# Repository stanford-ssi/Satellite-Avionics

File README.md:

# Satellite-Avionics

Welcome to SSI **Satellite Avionics**! Here, you can find everything you need to navigate our team! This repository covers weekly meeting times, technical trainings, team design documentation, assembly processes, testing procedures, and so much more!

**If you're new to Satellite Avionics, (and of course, are a stanford student), you should look through the [Satellite Avionics Onboarding Document](https://docs.google.com/document/d/1Evk9vAAE3cXXHKh05v-SdmLuFbIsvqwTA4ssfbo16VE/edit?tab=t.0) to get started on our team!**

If you have any questions, feel free to contact any AV Co-lead on Slack! Or feel free to email Kale, the current AV co-lead repo manager at **kalesrz@stanford.edu**.

# Current Leadership (Spring 2026 - Winter 2027)
Satellite Avionics Co-Leads: 
 * Clara Zhen (czhen@stanford.edu)
 * Nimalan Anbhuarasan (nimalan@stanford.edu)
 * Kale Suarez (kalesrz@stanford.edu)

Satellite Co-Leads: 
 * Amy Zheng (amyzheng@stanford.edu)
 * River Dowdy (rivdowdy@stanford.edu)
 * Carson Lauer (clauer@stanford.edu)

Workspace Manager: Clara Zhen
 - Contact For Questions Regarding ES3 and Durand Access

## Getting On Slack!
In order to join our weekly meetings, you'll need to join our slack to figure out where were meeting! You can join our slack by clicking [here](https://ssi-teams.slack.com/signup). Once you're on the slack, go ahead and add the [#satellite-avionics](https://ssi-teams.slack.com/archives/C2L29KW8J) channel. You should also make sure to join all of these important channels!
* [#satellite-avionics](https://ssi-teams.slack.com/archives/C2L29KW8J)
    - All AV communication and announcements happen here! You need to be in this channel to know
      where were meeting for the week.
* [#satellites](https://ssi-teams.slack.com/archives/C04JL94F9)
    - General Satellites team communications and announcements happen here!
* [#satellite-systems](https://ssi-teams.slack.com/archives/C4UL92684)
    - System-wide meeting plans and discussions with other subteams on Satellites happen here!
* [#esiii](https://ssi-teams.slack.com/archives/C3YLQTN87)
    - Our Lab Space!!!
* [#doorbell](https://ssi-teams.slack.com/archives/CE360LHD0)
    - If you don't have keycard access to End Station III (ES3), run the `\doorbell` command to get someone to come open the door if anyones in ES3.

## Weekly Meeting Times
Satellite Avionics has two official meetings each week:
**Weekly Avionics Meeting**
 * **Time:** Wednesday, 7:00 PM - 9:00 PM PST
 * **Location:** Check The [#Satellite-Avionics](https://ssi-teams.slack.com/archives/C2L29KW8J) channel in the slack for weekly meeting locations!
 * **Purpose:** Avionics meetings are specifically for AV-specific work, training, and discussions. AV member attendance is expected outside of conflicting Midterms or Finals. Fall quarter attendance is **mandatory** outside of class conflicts or personal health reasons.

**Satsurday Meetings**
 * **Time:** Saturday, 12:00 PM - 2:00 PM PST
 * **Location:** Check The [#Satellite-Avionics](https://ssi-teams.slack.com/archives/C2L29KW8J) channel in the slack for weekly meeting locations!
 * **Purpose**: Satsurday meetings are Satellite Avionics Full-Team work days! Every subteam will be meeting at this time. This can sometimes happen collectively and sometimes separately. Fall quarter will mostly be dedicated to AV specific onboarding training and early satellite development. Fall quarter attendance is **mandatory** outside of class conflicts or personal health reasons.

**Systems Meeting**
 * **Time:** Wednesday, 7:00 PM - 9:00 PM PST
 * **Location:** Check The [#Satellite-Systems](https://ssi-teams.slack.com/archives/C4UL92684) channel in the slack for weekly meeting locations!
 * **Purpose:** Systems meetings are where all major decisions about our satellite design occur and system-level planning and cross-team collaboration is planned. You are not obligated to come to these meetings if you are unable to, however, you should come to these meetings if you are available.

## Accessing Our Workspaces!
We primarily operate out of two buildings, End Station III (Deep Lab / Hepl South), and the Durand Aeronautics & Astronautics building. End Station III is a little difficult to find the first time, so please ask leads in the slack if you get lost!

### End Station III (Deep Lab / Hepl South)
**Address:** 491 S Service Rd, Stanford, CA 94305\
**Google Maps Link:** [Stanford Student Space Initiative](https://maps.app.goo.gl/ZUDnvgVmYYjSPFpS8)\
**Access Entrance:** Please enter through the **North Entrance** on Service Road (As Seen Below). After-Hours/Weekend Access requires that you obtain keycard access.

### Stanford University Aeronautics & Astronautics (Durand)
**Address:** 496 Lomita Mall, Stanford, CA 94305\
**Google Maps Link:** [Stanford University Aeronautics & Astronautics (Durand)](https://maps.app.goo.gl/TxbG7z5m1ypoC3tW7)\
**Access Entrance:** Any entrance can be used given you have obtained Durand keycard access. Otherwise, feel free to message a lead in the [#satellite-avionics](https://ssi-teams.slack.com/archives/C2L29KW8J) slack channel if you need help getting in!

### Gaining Access
To be able to gain keycard access to these workspaces and to be able to enter without another member to scan you in, you must complete the ES3 Lab safety trainings and complete all the steps listed on the [ES3 Access Guide](https://sites.google.com/stanford.edu/ssi/end-station-iii/keycard-access-for-es3). You will need to use your Stanford Email in order to view the guide.

## Additional Helpful Links / Quick Access
* [Stanford SSI Wiki: Satellites](https://ssi-wiki.stanford.edu/Category:Satellites)
    * SSI's official wiki page (notice: sometimes outdated, but there is some pretty useful information about the team and important definitions if you'd like to check it out.)\
* [SSI Slack Signup](https://ssi-teams.slack.com/signup)
* [ES3 Access Guide](https://sites.google.com/stanford.edu/ssi/end-station-iii/keycard-access-for-es3)

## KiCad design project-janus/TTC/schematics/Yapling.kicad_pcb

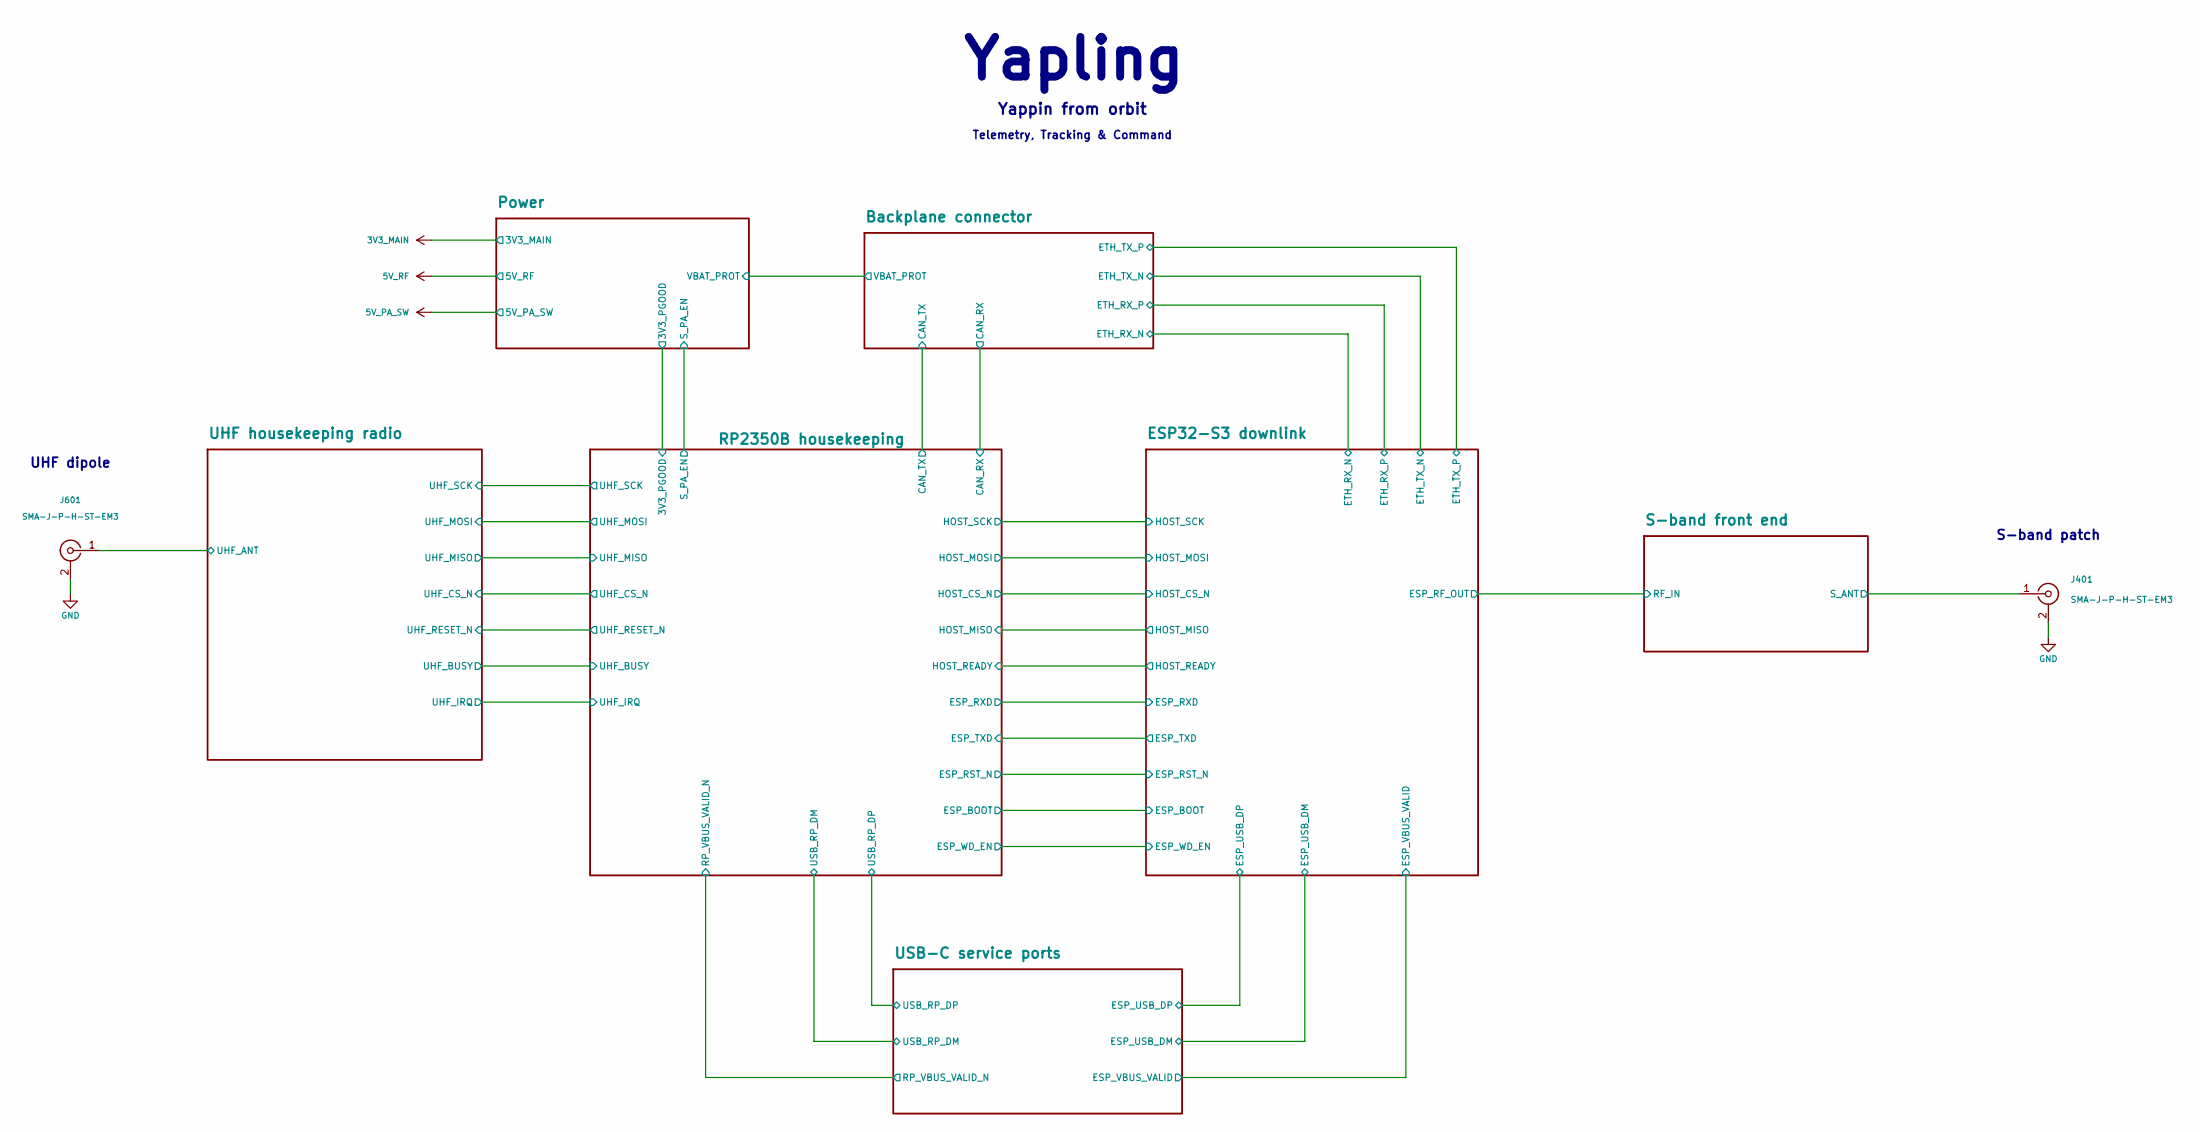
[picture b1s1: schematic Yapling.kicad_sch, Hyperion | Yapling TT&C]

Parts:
J401, J601: SMA-J-P-H-ST-EM3; Samtec_SMA_J_P_H_ST_EM3_DropInEdge; Rating 50 Ω, 335 V; MPN SMA-J-P-H-ST-EM3

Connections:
/S-band front end/S_ANT: J401.1 (In); also elsewhere on the board
/UHF housekeeping radio/UHF_ANT: J601.1 (In); also elsewhere on the board
GND: J401.2 (Ext), J601.2 (Ext); also elsewhere on the board

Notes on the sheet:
Yappin from orbit
Telemetry, Tracking & Command
UHF dipole
S-band patch
Yapling

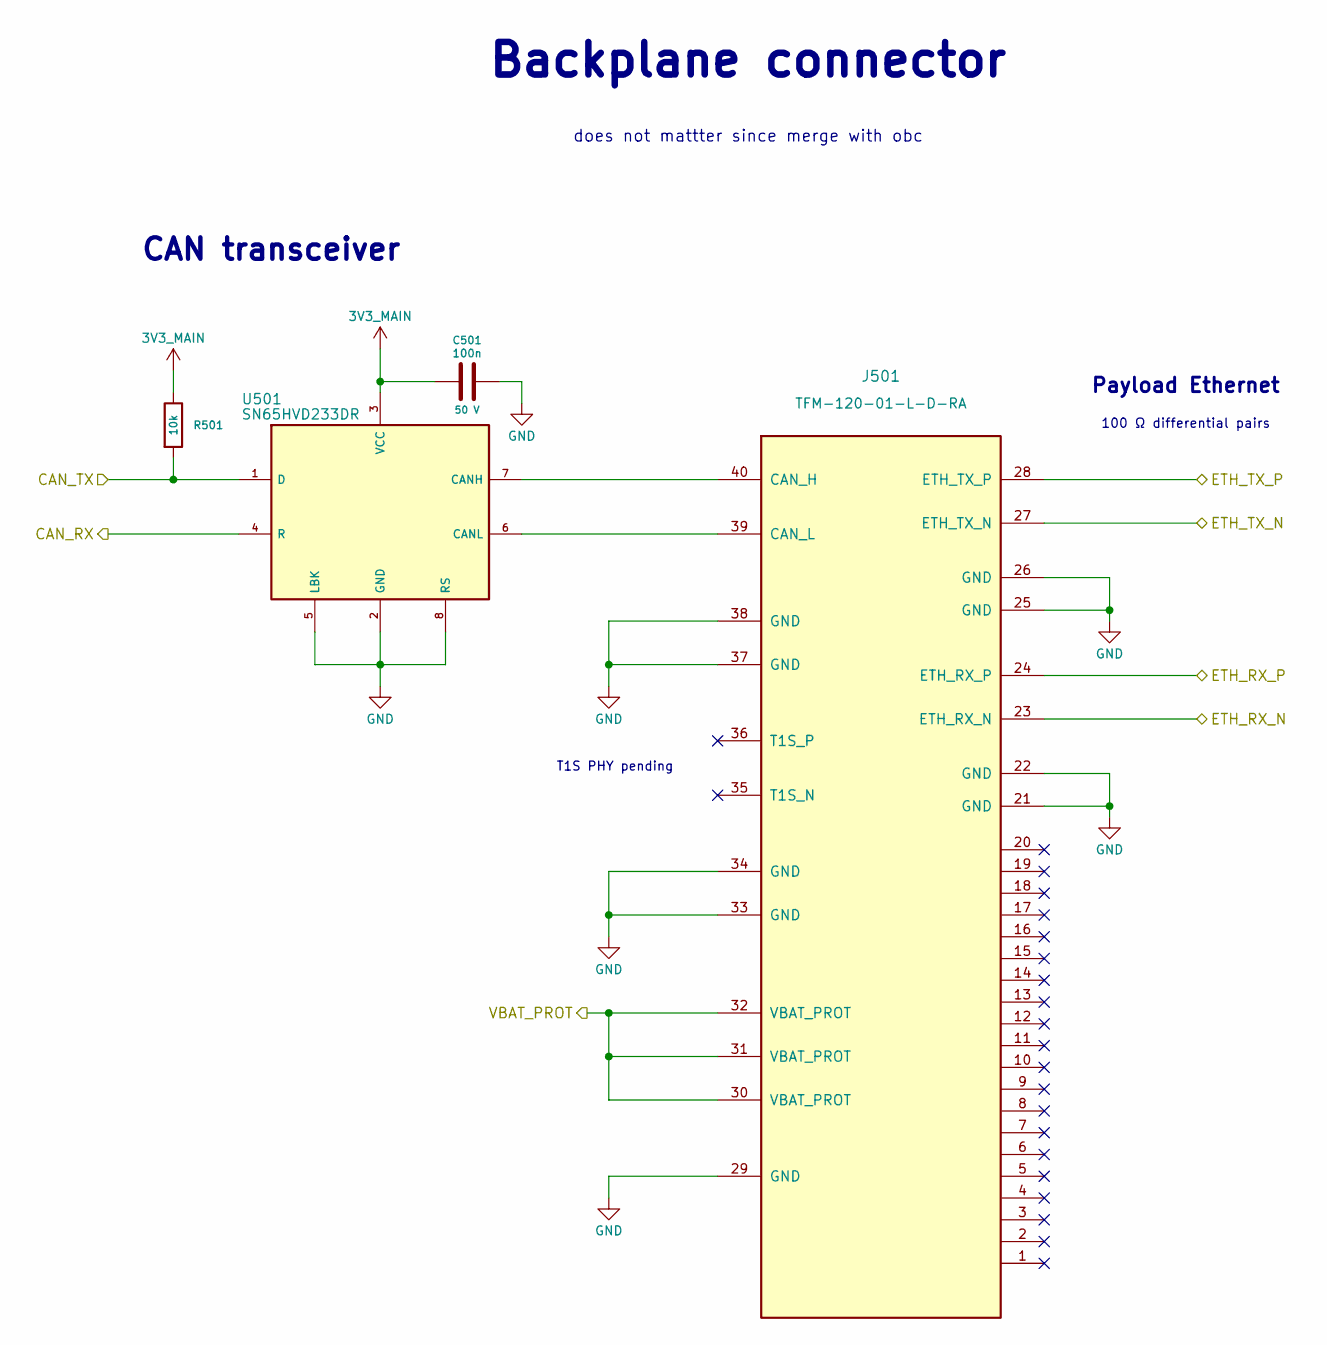
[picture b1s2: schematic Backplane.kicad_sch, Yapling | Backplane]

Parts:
C501: 100n; C_0402_1005Metric; Rating 50 V; Voltage 50 V; MPN GCM155R71H104KE02D
J501: TFM-120-01-L-D-RA; Rating 250 V AC; −55 to +125 °C; MPN TFM-120-01-L-D-RA
R501: 10k; R_0603_1608Metric; Rating 75 V; MPN TNPW060310K0BEEA
U501: SN65HVD233DR; Rating 3.0–3.6 V; MPN SN65HVD233DR

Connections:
3V3_MAIN: C501.1, R501.1, U501.3 (VCC); also elsewhere on the board
/Backplane connector/CAN_RX: U501.4 (R); also elsewhere on the board
/Backplane connector/CAN_TX: R501.2, U501.1 (D); also elsewhere on the board
/Backplane connector/ETH_RX_N: J501.23 (ETH_RX_N); also elsewhere on the board
/Backplane connector/ETH_RX_P: J501.24 (ETH_RX_P); also elsewhere on the board
/Backplane connector/ETH_TX_N: J501.27 (ETH_TX_N); also elsewhere on the board
/Backplane connector/ETH_TX_P: J501.28 (ETH_TX_P); also elsewhere on the board
GND: C501.2, J501.21 (GND), J501.22 (GND), J501.25 (GND), J501.26 (GND), J501.29 (GND), J501.33 (GND), J501.34 (GND), J501.37 (GND), J501.38 (GND), U501.2 (GND), U501.5 (LBK), U501.8 (RS); also elsewhere on the board
unnamed: J501.40 (CAN_H), U501.7 (CANH)
unnamed: J501.39 (CAN_L), U501.6 (CANL)
VBAT_PROT: J501.30 (VBAT_PROT), J501.31 (VBAT_PROT), J501.32 (VBAT_PROT); also elsewhere on the board

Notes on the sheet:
100 Ω differential pairs
Backplane connector
Payload Ethernet
does not mattter since merge with obc
T1S PHY pending
CAN transceiver

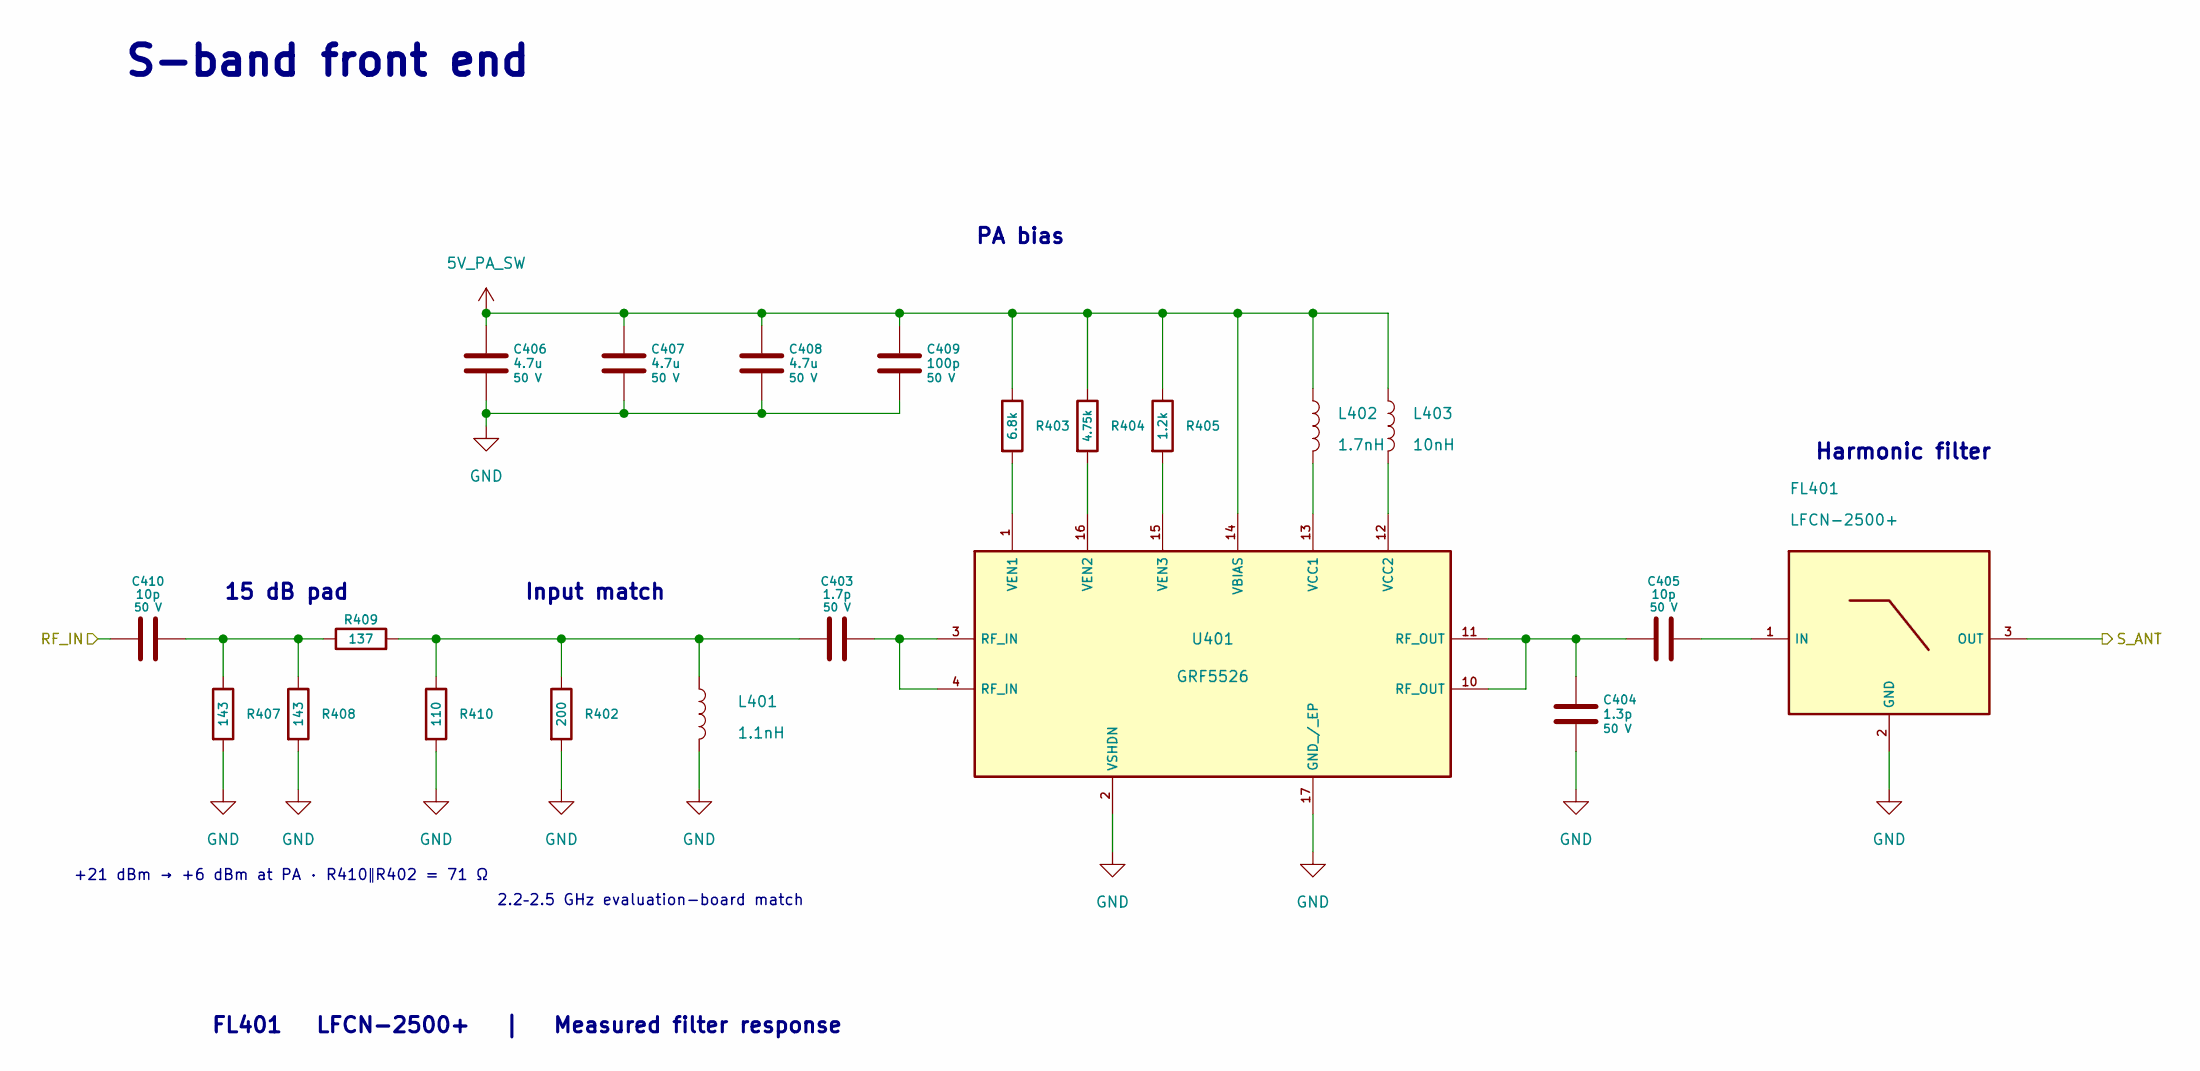
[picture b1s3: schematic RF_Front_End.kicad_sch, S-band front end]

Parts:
C403: 1.7p; C_0402_1005Metric; Rating 50 V, C0G; Voltage 50 V; MPN GJM1555C1H1R7BB01D
C404: 1.3p; C_0402_1005Metric; Rating 50 V, C0G; Voltage 50 V; MPN GJM1555C1H1R3BB01D
C405, C410: 10p; C_0402_1005Metric; Rating 50 V, C0G; Voltage 50 V; MPN GJM1555C1H100JB01D
C406, C407, C408: 4.7u; C_0805_2012Metric; Rating 50 V; Voltage 50 V; MPN C2012X7R1H475K125AC
C409: 100p; C_0402_1005Metric; Rating 50 V, C0G; Voltage 50 V; MPN GRM1555C1H101JA01D
FL401: LFCN-2500+; LFCN-2500; Rating 50 Ω, DC–2.5 GHz, 10 W maximum at 25 °C; MPN LFCN-2500+
L401: 1.1nH; L_0402_1005Metric; Rating 1.0 A; MPN LQG15HN1N1B02D
L402: 1.7nH; L_0402_1005Metric; Rating 640 mA; MPN LQW15AN1N7C00D
L403: 10nH; L_0603_1608Metric; Rating 1.6 A; MPN LQW18AN10NG80D
R402: 200; R_0402_1005Metric; Rating 50 V; MPN TNPW0402200RBEED
R403: 6.8k; R_0402_1005Metric; Rating 50 V; MPN TNPW04026K80BEED
R404: 4.75k; R_0402_1005Metric; Rating 50 V; MPN TNPW04024K75BEED
R405: 1.2k; R_0402_1005Metric; Rating 50 V; MPN TNPW04021K20BEED
R407, R408: 143; R_0402_1005Metric; Rating 50 V; MPN TNPW0402143RBEED
R409: 137; R_0402_1005Metric; Rating 50 V; MPN TNPW0402137RBEED
R410: 110; R_0402_1005Metric; Rating 50 V; MPN TNPW0402110RBEED
U401: GRF5526; Rating 4.0–5.5 V; MPN GRF5526

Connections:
5V_PA_SW: C406.1, C407.1, C408.1, C409.1, L402.1, L403.1, R403.1, R404.1, R405.1, U401.14 (VBIAS); also elsewhere on the board
/ESP32-S3 downlink/ESP_RF_OUT: C410.1; also elsewhere on the board
/S-band front end/S_ANT: FL401.3 (OUT); also elsewhere on the board
GND: C404.2, C406.2, C407.2, C408.2, C409.2, FL401.2 (GND), FL401.4 (GND), L401.2, R402.2, R407.2, R408.2, R410.2, U401.2 (VSHDN), U401.5 (GND/NC), U401.6 (GND/NC), U401.7 (GND/NC), U401.8 (GND/NC), U401.9 (GND/NC), U401.17 (GND_/_EP); also elsewhere on the board
unnamed: C403.1, L401.1, R402.1, R409.2, R410.1
unnamed: C403.2, U401.3 (RF_IN), U401.4 (RF_IN)
unnamed: C404.1, C405.1, U401.10 (RF_OUT), U401.11 (RF_OUT)
unnamed: C410.2, R407.1, R408.1, R409.1
unnamed: C405.2, FL401.1 (IN)
unnamed: L402.2, U401.13 (VCC1)
unnamed: L403.2, U401.12 (VCC2)
unnamed: R403.2, U401.1 (VEN1)
unnamed: R404.2, U401.16 (VEN2)
unnamed: R405.2, U401.15 (VEN3)

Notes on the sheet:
Input match
PA bias
FL401 LFCN-2500+ | Measured filter response
2.2–2.5 GHz evaluation-board match
S-band front end
Harmonic filter
15 dB pad
+21 dBm → +6 dBm at PA · R410∥R402 = 71 Ω

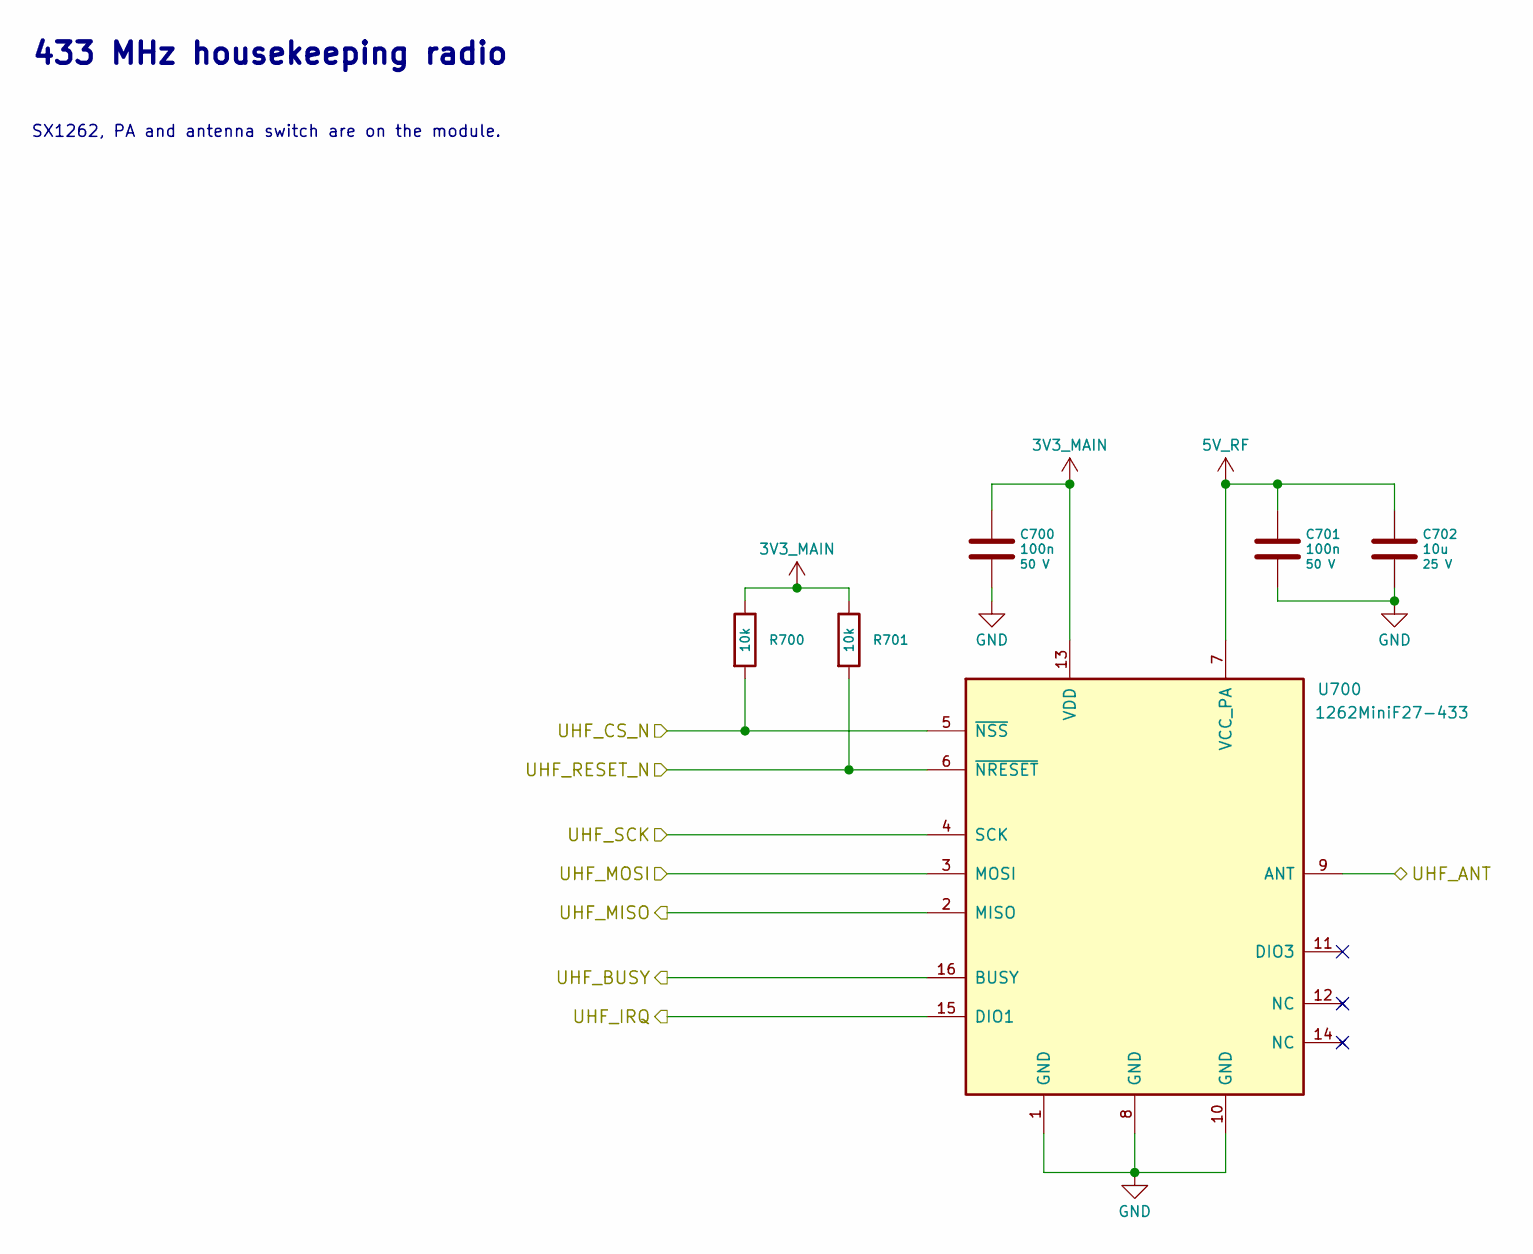
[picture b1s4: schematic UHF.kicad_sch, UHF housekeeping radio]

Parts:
C700, C701: 100n; C_0402_1005Metric; Rating 50 V; Voltage 50 V; MPN GCM155R71H104KE02D
C702: 10u; C_0805_2012Metric; Rating 25 V; Voltage 25 V; MPN C2012X7S1E106K125AE
R700, R701: 10k; R_0603_1608Metric; Rating 75 V; MPN TNPW060310K0BEEA
U700: 1262MiniF27-433; NiceRF_1262MiniF27; Rating 1.8–3.6 V logic, 3.3–5.0 V PA; MPN 1262MiniF27-433

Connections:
3V3_MAIN: C700.1, R700.1, R701.1, U700.13 (VDD); also elsewhere on the board
5V_RF: C701.1, C702.1, U700.7 (VCC_PA); also elsewhere on the board
/RP2350B housekeeping/UHF_BUSY: U700.16 (BUSY); also elsewhere on the board
/RP2350B housekeeping/UHF_CS_N: R700.2, U700.5 (~NSS); also elsewhere on the board
/RP2350B housekeeping/UHF_IRQ: U700.15 (DIO1); also elsewhere on the board
/RP2350B housekeeping/UHF_MISO: U700.2 (MISO); also elsewhere on the board
/RP2350B housekeeping/UHF_MOSI: U700.3 (MOSI); also elsewhere on the board
/RP2350B housekeeping/UHF_RESET_N: R701.2, U700.6 (~NRESET); also elsewhere on the board
/RP2350B housekeeping/UHF_SCK: U700.4 (SCK); also elsewhere on the board
/UHF housekeeping radio/UHF_ANT: U700.9 (ANT); also elsewhere on the board
GND: C700.2, C701.2, C702.2, U700.1 (GND), U700.8 (GND), U700.10 (GND); also elsewhere on the board

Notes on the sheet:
433 MHz housekeeping radio
SX1262, PA and antenna switch are on the module.

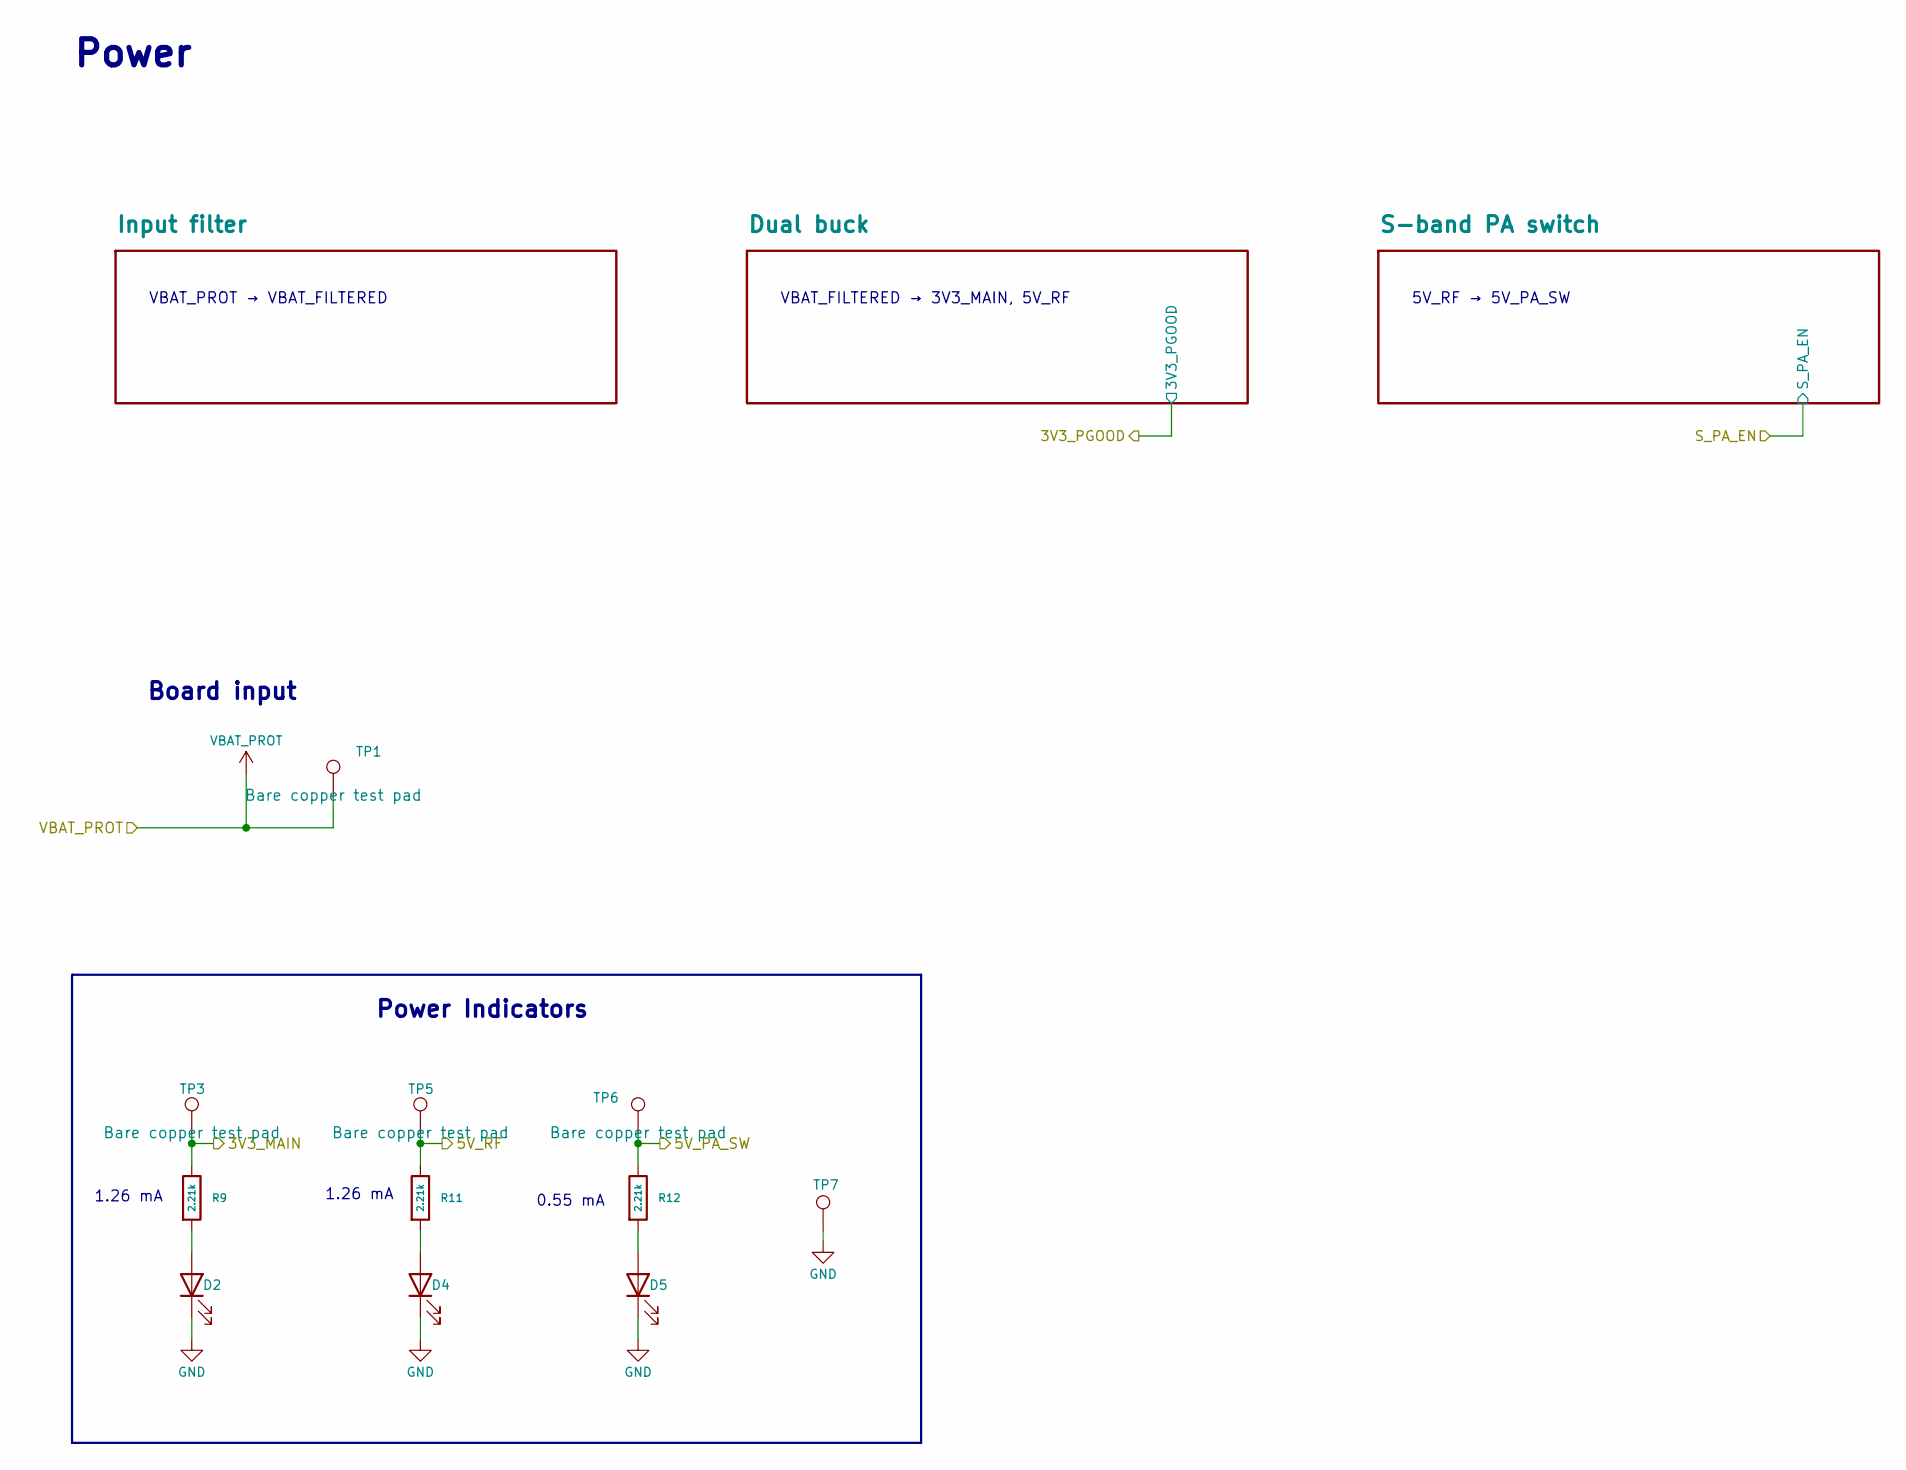
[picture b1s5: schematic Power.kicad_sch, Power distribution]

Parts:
D2, D4, D5: Green; LED_0603_1608Metric; Rating 2.1 V typ at 20 mA; MPN LTST-C190KGKT
R9, R11, R12: 2.21k; R_0603_1608Metric; Rating 75 V; MPN TNPW06032K21BEEA
TP1: VBAT_PROT; TestPoint_Pad_D1.0mm
TP3: 3V3_MAIN; TestPoint_Pad_D1.0mm
TP5: 5V_RF; TestPoint_Pad_D1.0mm
TP6: 5V_PA_SW; TestPoint_Pad_D1.0mm
TP7: GND; TestPoint_Keystone_5019_Miniature; Rating Miniature SMT silver-plated test point; MPN 5019

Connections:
3V3_MAIN: R9.1, TP3.1 (1_1); also elsewhere on the board
5V_PA_SW: R12.1, TP6.1 (1_1); also elsewhere on the board
5V_RF: R11.1, TP5.1 (1_1); also elsewhere on the board
GND: D2.1 (K), D4.1 (K), D5.1 (K), TP7.1 (1_1); also elsewhere on the board
unnamed: D2.2 (A), R9.2
unnamed: D4.2 (A), R11.2
unnamed: D5.2 (A), R12.2
VBAT_PROT: TP1.1 (1_1); also elsewhere on the board

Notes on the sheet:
VBAT_PROT → VBAT_FILTERED
Board input
1.26 mA
0.55 mA
Power
Power Indicators
VBAT_FILTERED → 3V3_MAIN, 5V_RF
5V_RF → 5V_PA_SW

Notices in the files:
parts and their libraries:
LGA-56 exposed-pad package, 7x7 mm, 0.4 mm pitch, for ESP32-S3-PICO-1; Espressif KiCad Libraries d5b68fd, CC BY-SA 4.0 with design exception (github.com/espressif/kicad-libraries/blob/d5b68fd/LICENSE.md). STEP added from Espressif package drawing Fig. 6-1.
